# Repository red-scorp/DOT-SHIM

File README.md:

# DOT-SHIM project

DOT-SHIM (mini-HAT), a DIY 2.54mm raster board for Raspberry Pi.

Some time ago I have tried to attach something self-made schematics to a zero Pi with some limited success.
Here I've designed a 2.54mm raster board for DIY applications.

## DOT-SHIM

Raspberry Pi 40-pin **DOT-SHIM** mini-HAT.

Preview:

[Schematics in PDF format](doc/DOT-SHIM.pdf)

Features:

- locked Pi headers
- 2.54mm (0.1") raster holes
- clear pin description
- double set of Pi headers (for inside and outside mount)
- can be used as SHIM (no headers) or HAT (with headers) 

CAM files are available.

## DOT-zero-SHIM

Raspberry Pi zero 40-pin **DOT-zero-SHIM** mini-HAT.

Preview:

[Schematics in PDF format](doc/DOT-zero-SHIM.pdf)

Features:

- locked Pi headers
- 2.54mm (0.1") raster holes
- clear pin description
- Pi zero board style
- can be used as SHIM (no headers) or HAT (with headers)

CAM files are available.

## DOT-plus-SHIM

Raspberry Pi A+/B+ 40-pin **DOT-plus-SHIM** mini-HAT.

Preview:

[Schematics in PDF format](doc/DOT-plus-SHIM.pdf)

Features:

- locked Pi headers
- 2.54mm (0.1") raster holes
- clear pin description
- Pi A+/B+ board style
- can be used as SHIM (no headers) or HAT (with headers)

CAM files are available.

## DOT-simple-SHIM

Raspberry Pi 40-pin **DOT-simple-SHIM** mini-HAT.

Preview:

[Schematics in PDF format](doc/DOT-simple-SHIM.pdf)

Features:

- locked Pi headers
- a row of 2.54mm (0.1") raster holes
- extended pin description
- can be used as SHIM (no headers) or HAT (with headers)

CAM files are available.

## Links

- [pinout.xyz](https://pinout.xyz/) - a brilliant resource on topic of Pi's pinout and HATs.
- [raspberrypi/hats](https://github.com/raspberrypi/hats) - Pi's HAT specification.

## How to help

Your contributions as code, resources, or finances are welcome! Please contact me directly via email at andriy.golovnya@gmail.com or through my [GitHub profile](https://github.com/red-scorp).

If you'd like to make a financial contribution, you can donate via [PayPal](http://paypal.me/redscorp) or [Ko-Fi](http://ko-fi.com/redscorp). Your support is greatly appreciated.

Thanks in advance!

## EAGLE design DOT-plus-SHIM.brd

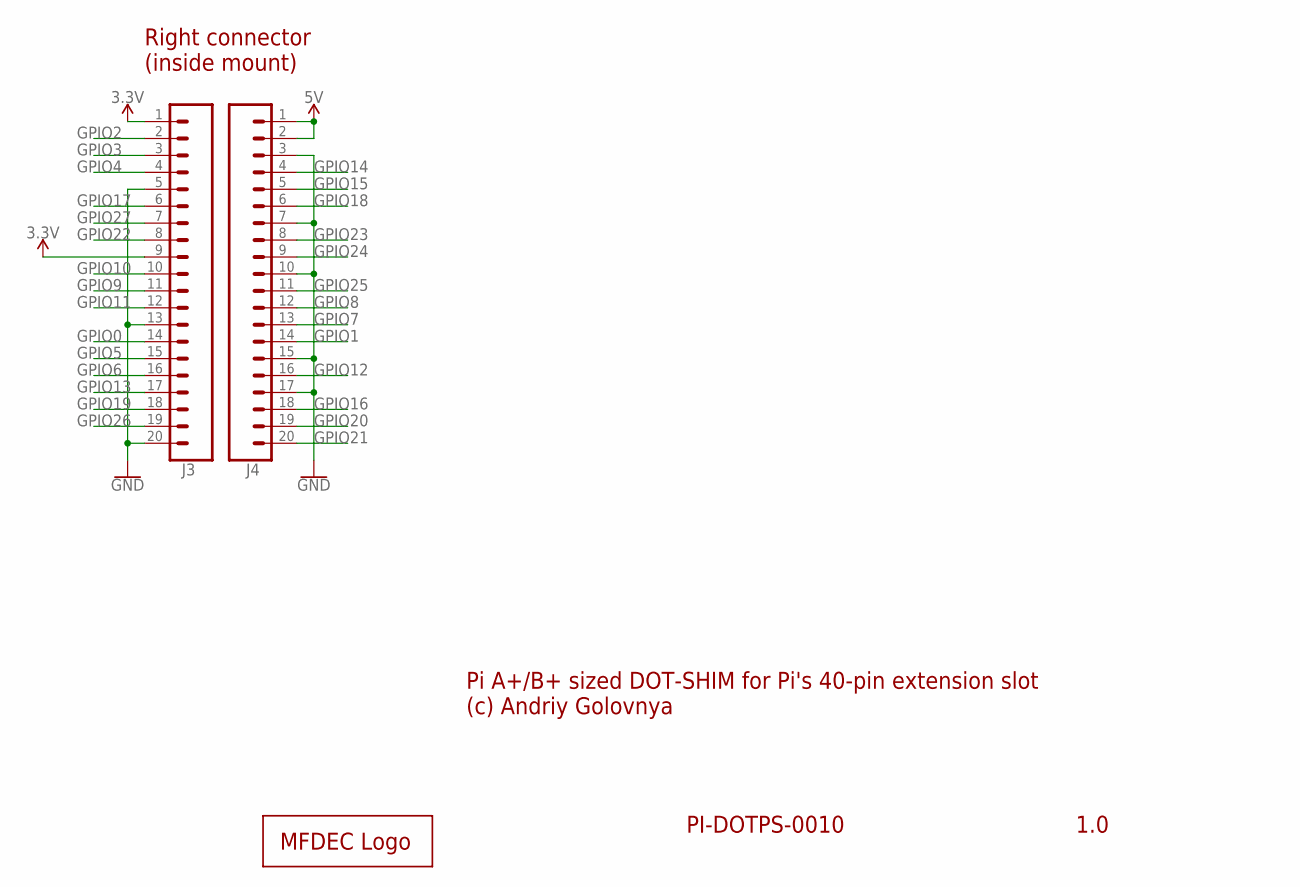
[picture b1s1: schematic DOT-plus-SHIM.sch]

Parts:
J3, J4: CONN_20LOCK; 1X20_LOCK
LOGO1: MFDECLOGO_L_40MM; MFDEC_L_40MM

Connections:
3.3V: J3.1, J3.9
5V: J4.1, J4.2
GND: J3.5, J3.13, J3.20, J4.3, J4.7, J4.10, J4.15, J4.17
GPIO0: J3.14
GPIO1: J4.14
GPIO2: J3.2
GPIO3: J3.3
GPIO4: J3.4
GPIO5: J3.15
GPIO6: J3.16
GPIO7: J4.13
GPIO8: J4.12
GPIO9: J3.11
GPIO10: J3.10
GPIO11: J3.12
GPIO12: J4.16
GPIO13: J3.17
GPIO14: J4.4
GPIO15: J4.5
GPIO16: J4.18
GPIO17: J3.6
GPIO18: J4.6
GPIO19: J3.18
GPIO20: J4.19
GPIO21: J4.20
GPIO22: J3.8
GPIO23: J4.8
GPIO24: J4.9
GPIO25: J4.11
GPIO26: J3.19
GPIO27: J3.7

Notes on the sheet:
1.0
PI-DOTPS-0010
Pi A+/B+ sized DOT-SHIM for Pi's 40-pin extension slot (c) Andriy Golovnya
Right connector (inside mount)

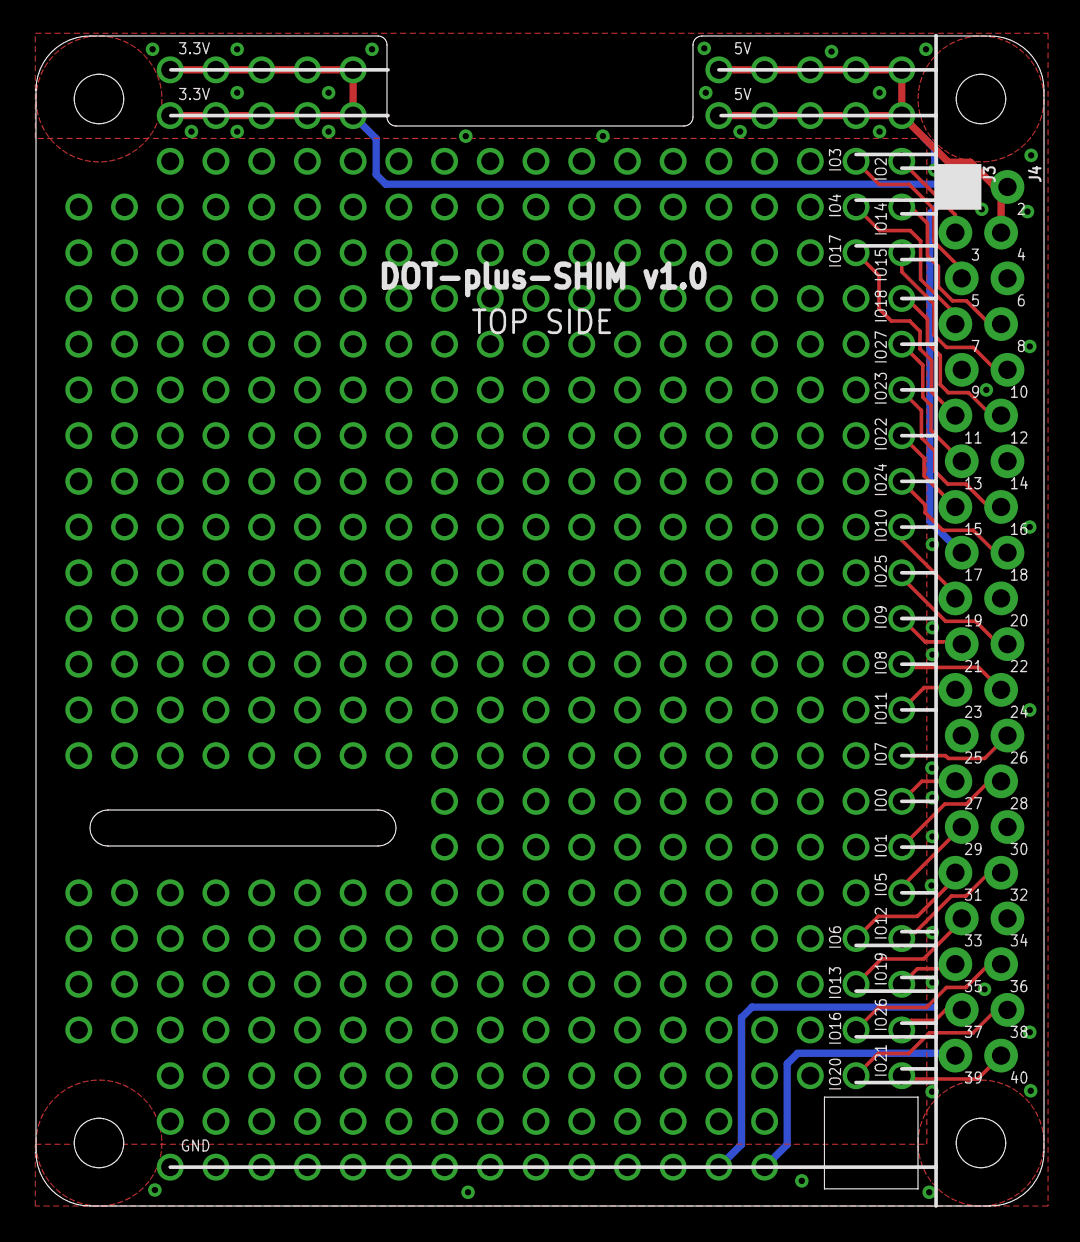
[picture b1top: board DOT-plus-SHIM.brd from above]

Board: 2 copper layers, 56.0 x 65.0 mm, 3 parts (1 on the bottom side), 3 nets.

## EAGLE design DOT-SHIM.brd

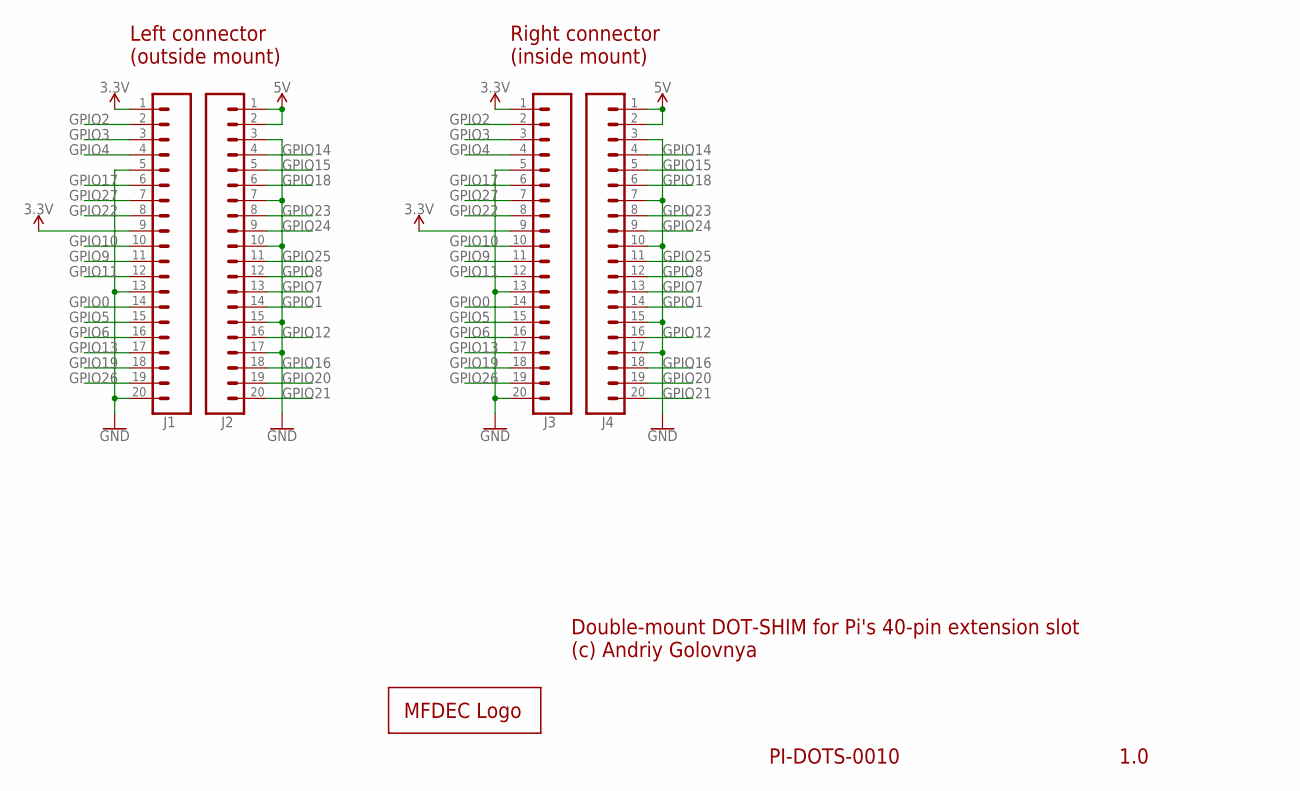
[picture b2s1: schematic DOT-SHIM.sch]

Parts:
J1, J2, J3, J4: CONN_20LOCK; 1X20_LOCK
LOGO2: MFDECLOGO_L_20MM; MFDEC_L_20MM

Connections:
3.3V: J1.1, J1.9, J3.1, J3.9
5V: J2.1, J2.2, J4.1, J4.2
GND: J1.5, J1.13, J1.20, J2.3, J2.7, J2.10, J2.15, J2.17, J3.5, J3.13, J3.20, J4.3, J4.7, J4.10, J4.15, J4.17
GPIO0: J1.14, J3.14
GPIO1: J2.14, J4.14
GPIO2: J1.2, J3.2
GPIO3: J1.3, J3.3
GPIO4: J1.4, J3.4
GPIO5: J1.15, J3.15
GPIO6: J1.16, J3.16
GPIO7: J2.13, J4.13
GPIO8: J2.12, J4.12
GPIO9: J1.11, J3.11
GPIO10: J1.10, J3.10
GPIO11: J1.12, J3.12
GPIO12: J2.16, J4.16
GPIO13: J1.17, J3.17
GPIO14: J2.4, J4.4
GPIO15: J2.5, J4.5
GPIO16: J2.18, J4.18
GPIO17: J1.6, J3.6
GPIO18: J2.6, J4.6
GPIO19: J1.18, J3.18
GPIO20: J2.19, J4.19
GPIO21: J2.20, J4.20
GPIO22: J1.8, J3.8
GPIO23: J2.8, J4.8
GPIO24: J2.9, J4.9
GPIO25: J2.11, J4.11
GPIO26: J1.19, J3.19
GPIO27: J1.7, J3.7

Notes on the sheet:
1.0
PI-DOTS-0010
Double-mount DOT-SHIM for Pi's 40-pin extension slot (c) Andriy Golovnya
Left connector (outside mount)
Right connector (inside mount)

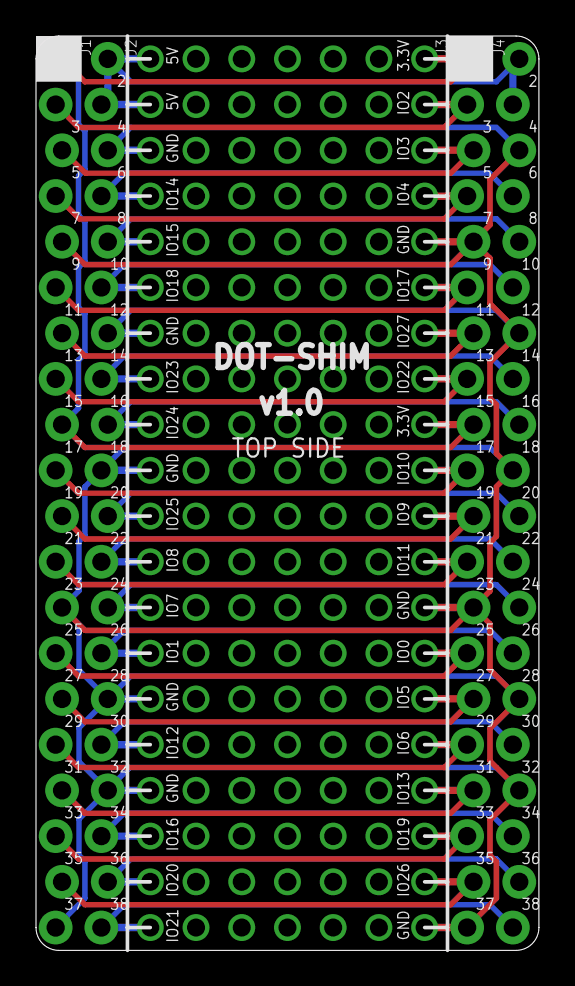
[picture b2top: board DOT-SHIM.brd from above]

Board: 2 copper layers, 27.9 x 50.8 mm, 5 parts (1 on the bottom side), 31 nets.

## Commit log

2021-01-08 Added DOT-SHIM (2.54mm raster board)
2021-01-08 Generated CAM files. Generated PNG preview image. Generated PDF schematics.
2021-01-08 Updated description and added README.
2021-01-08 Add FUNDING.yml
2021-01-08 Updated descriptions.
2021-01-10 Visual changes.
2021-01-10 Added DOT-zero-SHIM board. Generated CAM. Generated PNG preview image. Generated PDF schematics.
2021-01-10 Added DOT-plus-SHIM board. Generated CAM. Generated PNG preview image. Generated PDF schematics.
2021-01-10 Added link to raspberrypi/hats
2021-01-11 Reworked A+/B+ board corners
2021-01-11 Reworked zero board corners
2021-01-11 Generated proper PNG preview. Fix some minor stuff.
2021-01-11 Fix some minor stuff.
2021-01-13 Fixed description
2021-01-14 Added DOT-simple-SHIM board. Generated CAM. Generated PDF schematics. Generated PNG preview image.
2021-01-29 Made pin labeling bigger. Generated new CAM.
2021-01-30 Made text labels in 3D-style (copper + silk) on DOT-simple-SHIM. Generated new CAM.
2021-01-30 Made label text a bit thicker. Generated new CAM.
2021-01-30 Generated PNG preview image.
2021-03-03 Fix DESCRIPTION.
2021-07-29 Make round cutouts in screwing area. Generated CAM files. Generated PNG previews.
2021-12-05 cleanup.
2022-01-24 Added Ko-Fi link
2022-02-06 Updated descriptions
2022-03-16 Fixed DRC
2023-08-28 Updated 'How to help' section.

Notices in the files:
parts and their libraries:
SparkFun-PowerSymbols: Licensing: Creative Commons ShareAlike 4.0 International - https://creativecommons.org/licenses/by-sa/4.0
